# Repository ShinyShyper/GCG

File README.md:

# Gesture Control Glove

Diplomarbeit, HTL Mödling/Mechatronik
2018/19

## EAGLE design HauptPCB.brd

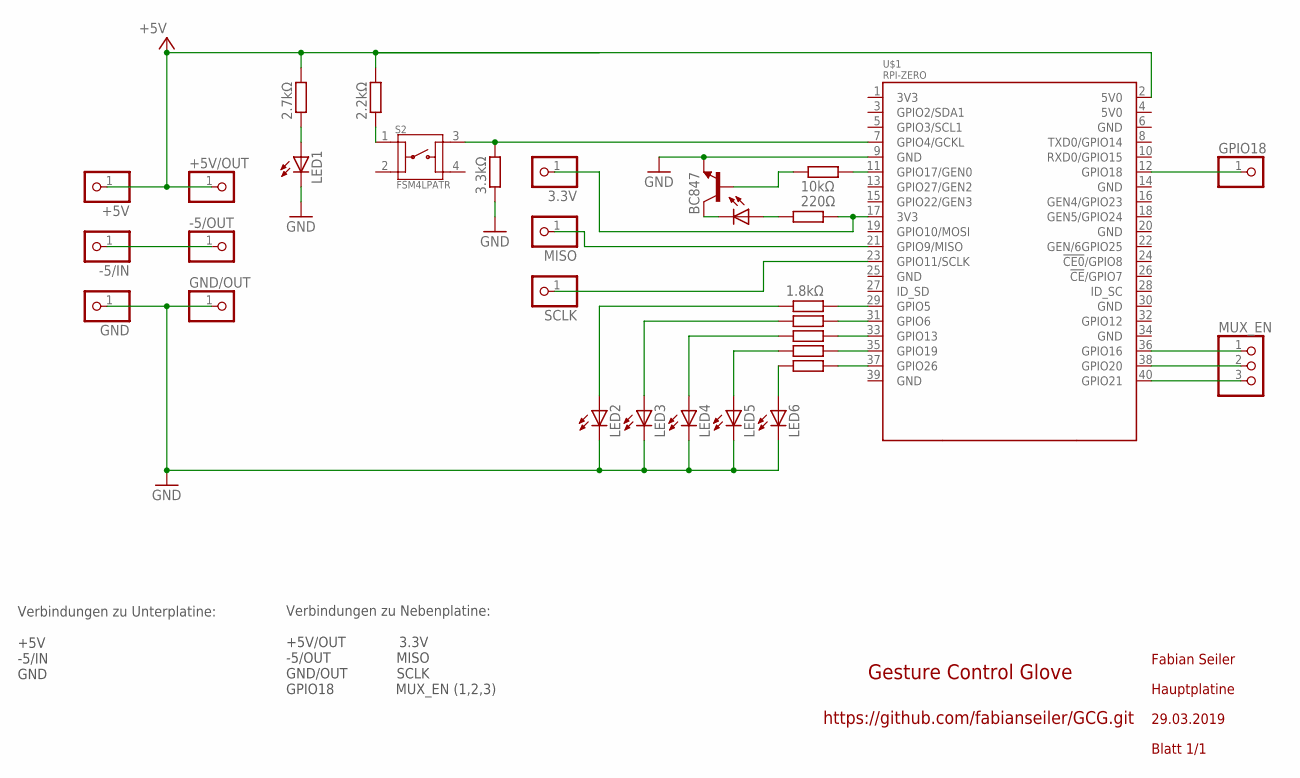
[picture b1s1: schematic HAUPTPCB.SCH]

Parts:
3.3V: PINHD-1X1CB; 1X01-CLEANBIG
+5V, +5V/OUT: PINHD-1X1CB; 1X01-CLEANBIG
-5/IN, -5/OUT: PINHD-1X1CB; 1X01-CLEANBIG
GND: PINHD-1X1CB; 1X01-CLEANBIG
GND/OUT: PINHD-1X1CB; 1X01-CLEANBIG
GPIO18: PINHD-1X1CB; 1X01-CLEANBIG
LED1, LED2, LED3, LED4, LED5, LED6: LED_ESML0603; LED_SML0603
LED_IR: LED_ELD260; LED_LD260
MISO: PINHD-1X1CB; 1X01-CLEANBIG
MUX_EN: PINHD-1X3CB; 1X03-CLEANBIG
RL1: 1.8kΩ; R0402
RL2, RL3, RL4, RL5: R-EU_R0402; R0402
R_IR1: 10kΩ; R0402
R_IR2: 220Ω; R0402
R_TTP1: 2.7kΩ; R0402
R_TTP9: 2.2kΩ; R0402
R_TTP10: 3.3kΩ; R0402
S2: FSM4LPATR; SW_FSM4LPATR
SCLK: PINHD-1X1CB; 1X01-CLEANBIG
T1: BC847; SOT23
U$1: RPI-ZERO; RASPBERRYPI_BASTELSTUBE_V13_RASPI_BOARD_B+_FULL

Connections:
3V3@2: 3.3V.1, R_IR2.2, U$1.17 (3V3)
+5V: +5V.1, +5V/OUT.1, R_TTP1.2, R_TTP9.2, U$1.2 (5V0)
GND: GND.1, GND/OUT.1, LED1.C, LED2.C, LED3.C, LED4.C, LED5.C, LED6.C, R_TTP10.1, T1.2 (E), U$1.9 (GND)
unnamed: -5/IN.1, -5/OUT.1
unnamed: LED_IR.K (C), T1.3 (C)
unnamed: MISO.1, U$1.21 (GPIO9/MISO)
unnamed: MUX_EN.3, U$1.40 (GPIO21)
unnamed: R_IR1.2, U$1.11 (GPIO17/GEN0)
unnamed: LED1.A, R_TTP1.1
unnamed: LED_IR.A, R_IR2.1
unnamed: R_TTP10.2, S2.3, U$1.7 (GPIO4/GCKL)
unnamed: LED5.A, RL4.1
unnamed: SCLK.1, U$1.23 (GPIO11/SCLK)
unnamed: LED4.A, RL3.1
unnamed: LED6.A, RL5.1
unnamed: LED3.A, RL2.1
unnamed: LED2.A, RL1.1
unnamed: MUX_EN.2, U$1.38 (GPIO20)
unnamed: MUX_EN.1, U$1.36 (GPIO16)
unnamed: GPIO18.1, U$1.12 (GPIO18)
unnamed: RL5.2, U$1.37 (GPIO26)
unnamed: RL4.2, U$1.35 (GPIO19)
unnamed: RL3.2, U$1.33 (GPIO13)
unnamed: RL1.2, U$1.29 (GPIO5)
unnamed: RL2.2, U$1.31 (GPIO6)
unnamed: R_IR1.1, T1.1 (B)
unnamed: R_TTP9.1, S2.1

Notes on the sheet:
Verbindungen zu Unterplatine: +5V -5/IN GND
Verbindungen zu Nebenplatine: +5V/OUT 3.3V -5/OUT MISO GND/OUT SCLK GPIO18 MUX_EN (1,2,3)
Fabian Seiler
Hauptplatine
29.03.2019
Gesture Control Glove
https://github.com/fabianseiler/GCG.git
Blatt 1/1

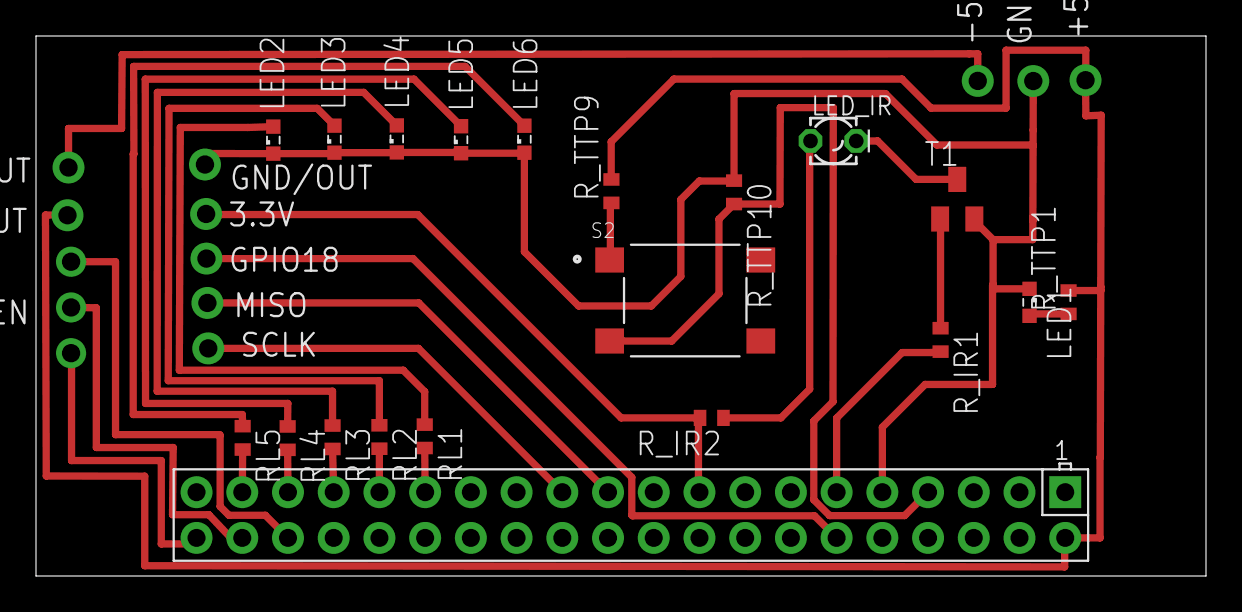
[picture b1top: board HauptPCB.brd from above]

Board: 2 copper layers, 65.0 x 30.0 mm, 31 parts (0 on the bottom side), 27 nets.

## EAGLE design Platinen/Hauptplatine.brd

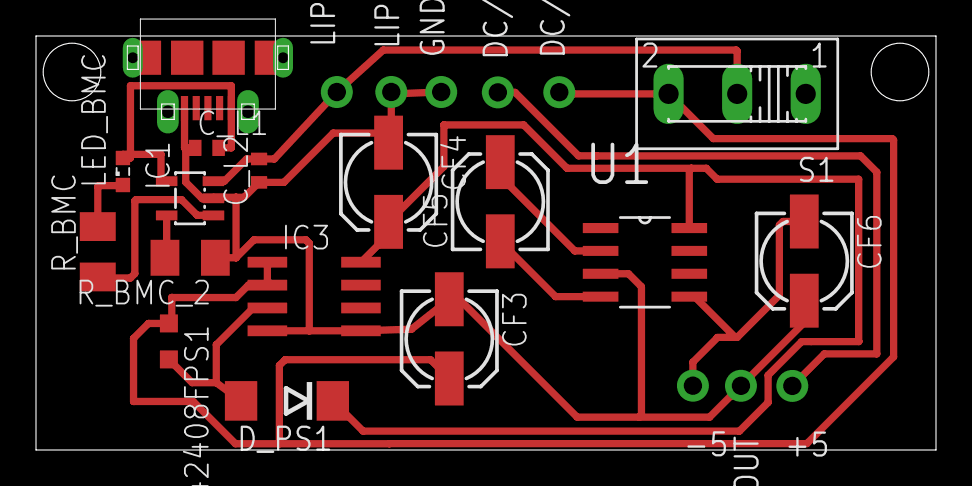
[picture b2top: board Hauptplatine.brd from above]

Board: 2 copper layers, 50.0 x 23.0 mm, 24 parts (0 on the bottom side), 13 nets.

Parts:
+5: 1X01-CLEANBIG
-5: 1X01-CLEANBIG
CF3, CF5, CF6: 10uF; 153CLV-0505
CF4: 33uF; 153CLV-0505
C_L1, C_L2: 4,7uF; C0402
DC/IN: 1X01-CLEANBIG
DC/OUT: 1X01-CLEANBIG
D_PS1: DO214AA
GND/IN: 1X01-CLEANBIG
GND/OUT: 1X01-CLEANBIG
IC1: MCP73831/OT; SOT23-5L
IC3: LT1111CS8; SO08
L-242408FPS1: 22uH; L2012C
LED_BMC: LED_SML0603
LIPO+: 1X01-CLEANBIG
LIPO-: 1X01-CLEANBIG
R_BMC: 470Ω; M1206
R_BMC_2: 2kΩ; M1206
S1: 255SB
U1: ICL7660ACBAZA-T; SOIC127P600X175-8N
U$2: MICRO-USB-RECEPTACLE47589-0001; 47589-0001

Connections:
+5V: +5.1, DC/OUT.1
-5V: -5.1, CF6.-, U1.5
GND: CF3.-, CF4.-, CF6.+, C_L1.1, C_L2.1, GND/IN.1, GND/OUT.1, IC1.2, IC3.4, IC3.5, LIPO-.1, R_BMC_2.1, U1.3, U$2.5
unnamed: CF3.+, DC/IN.1, IC3.1, IC3.2, L-242408FPS1.1, S1.3
unnamed: CF5.-, U1.4
unnamed: CF5.+, U1.2
unnamed: C_L1.2, IC1.4, LED_BMC.A, U$2.1
unnamed: LED_BMC.C, R_BMC.2
unnamed: IC1.1, R_BMC.1
unnamed: IC1.5, R_BMC_2.2
unnamed: C_L2.2, IC1.3, LIPO+.1, S1.2
unnamed: D_PS1.A, IC3.3, L-242408FPS1.2
unnamed: CF4.+, D_PS1.C, IC3.8, U1.8

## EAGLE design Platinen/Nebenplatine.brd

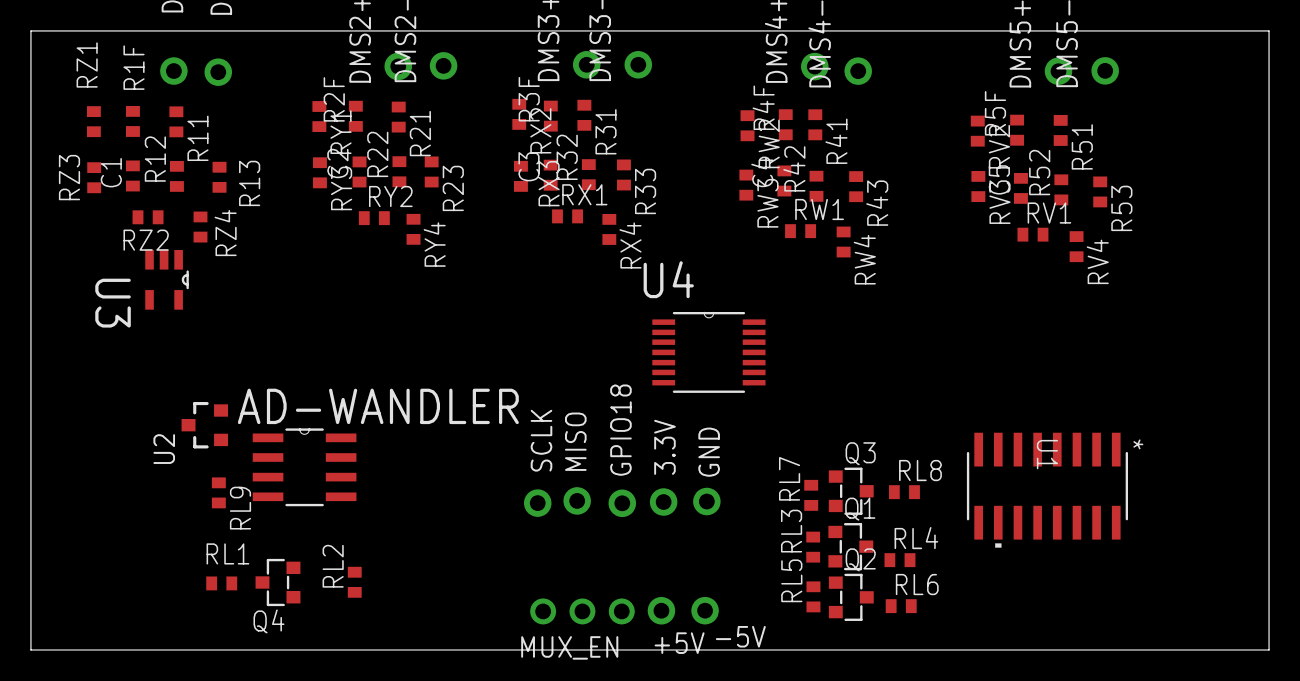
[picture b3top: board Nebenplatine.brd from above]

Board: 2 copper layers, 80.0 x 40.0 mm, 81 parts (0 on the bottom side), 46 nets, no tracks yet.

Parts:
3.3V: 1X01-CLEANBIG
+5V: 1X01-CLEANBIG
-5V: 1X01-CLEANBIG
AD-WANDLER: MCP3201-CI/SN; SOIC127P600X175-8N
C1: 0,1uF; C0402
C2, C3, C4, C5: C0402
DMS1+, DMS1-, DMS2+, DMS2-, DMS3+, DMS3-, DMS4+, DMS4-, DMS5+, DMS5-: 1X01-CLEANBIG
GND: 1X01-CLEANBIG
GPIO18: 1X01-CLEANBIG
MISO: 1X01-CLEANBIG
MUX_EN: 1X03-CLEANBIG
Q1, Q2, Q3, Q4: BSS138; SOT23
R1F: 100k; R0402
R2F, R3F, R4F, R5F: ???Ω; R0402
R11, R12, R13, R21, R22, R23, R31, R32, R33, R41, R42, R43, R51, R52, R53: 350Ω; R0402
RL1, RL2, RL3, RL4, RL5, RL6, RL7, RL8: 10kΩ; R0402
RL9: 220Ω; R0402
RV1: 1kΩ; R0402
RV2, RV3: 10kΩ; R0402
RV4: 100kΩ; R0402
RW1: 1kΩ; R0402
RW2, RW3: 10kΩ; R0402
RW4: 100kΩ; R0402
RX1: 1kΩ; R0402
RX2, RX3: 10kΩ; R0402
RX4: 100kΩ; R0402
RY1, RY3: 10kΩ; R0402
RY2: 1kΩ; R0402
RY4: 100kΩ; R0402
RZ1, RZ3: 10kΩ; R0402
RZ2: 1kΩ; R0402
RZ4: 100kΩ; R0402
SCLK: 1X01-CLEANBIG
U1: SN74HC4851-Q1_D_16; D16
U2: LM4040; SOT23-3
U3: OPA354AQDBVRQ1; SOT95P280X145-5N
U4: OPA4354AIPWR; SOP65P640X120-14N

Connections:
+5V: +5V.1, AD-WANDLER.8, R11.2, R12.2, R21.2, R22.2, R31.2, R32.2, R41.2, R42.2, R51.2, R52.2, RL1.1, RL4.2, RL6.2, RL8.2, RL9.2, U1.16, U3.5, U4.4
-5V: -5V.1, U3.2, U4.11
GND: AD-WANDLER.3, AD-WANDLER.4, DMS1-.1, DMS2-.1, DMS3-.1, DMS4-.1, DMS5-.1, GND.1, R13.1, R23.1, R33.1, R43.1, R53.1, RV3.2, RW3.2, RX3.2, RY3.2, RZ3.2, U1.8, U2.2
unnamed: AD-WANDLER.7, SCLK.1
unnamed: AD-WANDLER.6, MISO.1
unnamed: 3.3V.1, Q1.1, Q2.1, Q3.1, Q4.1, RL2.1, RL3.2, RL5.2, RL7.2
unnamed: AD-WANDLER.1, RL9.1, U2.1
unnamed: C1.2, R1F.2, RZ1.2
unnamed: DMS2+.1, R2F.2, R21.1
unnamed: RY1.2, RY3.1, U4.3
unnamed: MUX_EN.3, Q2.2, RL5.1
unnamed: Q1.3, RL4.1, U1.9
unnamed: GPIO18.1, Q4.2, RL2.2
unnamed: AD-WANDLER.2, U1.3
unnamed: MUX_EN.1, Q3.2, RL7.1
unnamed: Q2.3, RL6.1, U1.10
unnamed: MUX_EN.2, Q1.2, RL3.1
unnamed: Q3.3, RL8.1, U1.11
unnamed: AD-WANDLER.5, Q4.3, RL1.2
unnamed: C1.1, R12.1, R13.2, RZ2.2
unnamed: RX2.2, RX3.1, U4.5
unnamed: RY2.2, RY4.1, U4.2
unnamed: C3.1, R32.1, R33.2, RX1.1
unnamed: C4.1, R42.1, R43.2, RW1.1
unnamed: DMS3+.1, R3F.2, R31.1
unnamed: DMS1+.1, R1F.1, R11.1
unnamed: RZ1.1, RZ3.1, U3.3
unnamed: RZ2.1, RZ4.1, U3.4
unnamed: C5.2, R5F.1, RV2.1
unnamed: DMS4+.1, R4F.2, R41.1
unnamed: C4.2, R4F.1, RW2.1
unnamed: DMS5+.1, R5F.2, R51.1
unnamed: C2.2, R2F.1, RY1.1
unnamed: C2.1, R22.1, R23.2, RY2.1
unnamed: C3.2, R3F.1, RX2.1
unnamed: RX1.2, RX4.1, U4.6
unnamed: C5.1, R52.1, R53.2, RV1.1
unnamed: RW2.2, RW3.1, U4.9
unnamed: RV2.2, RV3.1, U4.12
unnamed: RW1.2, RW4.1, U4.10
unnamed: RV1.2, RV4.1, U4.13
unnamed: RW4.2, U1.1, U4.8
unnamed: RY4.2, U1.15, U4.1
unnamed: RX4.2, U1.12, U4.7
unnamed: RZ4.2, U1.14, U3.1
unnamed: RV4.2, U1.5, U4.14

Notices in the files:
parts and their libraries:
con-molex-usb: (C) 2014 Tomasz Boleslaw CEDRO, cederom@tlen.pl, http://www.tomek.cedro.info.
